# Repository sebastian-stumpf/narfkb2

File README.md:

# narfkb2

More pictures in the `pictures` directory.

## Attention

I'm a hobbyist/amateur at best. So there may be things that aren't optimized. That being said I've had the files
in the `gerbers/` directory manufactured at JLC with 1.6mm size and they work just fine with my fork of the qmk repository
directory. So if you decide to use this, then please be advised that I'm not providing any sort of liability and you should
exercise some caution.

## BOM

| Quantity  | Item                               | Comment                  |
| --------- | ---------------------------------- | ------------------------ |
| 2         | Waveshare RP2040-Zero              |                          |
| 2         | IC-Sockets for MCU                 | Optional but recommended |
| 2         | TRRS Sockets                       |                          |
| 50        | 1N4148 SOD123 diodes               |                          |
| 42        | MX Hotswap Sockets                 |                          |
| 2         | EC11 Encoders                      |                          |
| 6         | Omrom 6mm Tact switches            | B3F-1002                 |
| 42        | MX Switches + Keycaps              |                          |
| 12        | M2 Screws, Nuts, Bolts and Spacers |                          |

## Firmware

See [my fork](https://github.com/sebastian-stumpf/qmk_firmware/tree/sepp/keyboards/narfkb2) of the qmk repository. Nothing special here.
You can just copy the code over to your own repository.

## Feedback

I'm always happy to hear your opinions about this and if you decide to build this board then please do send me a picture of it.

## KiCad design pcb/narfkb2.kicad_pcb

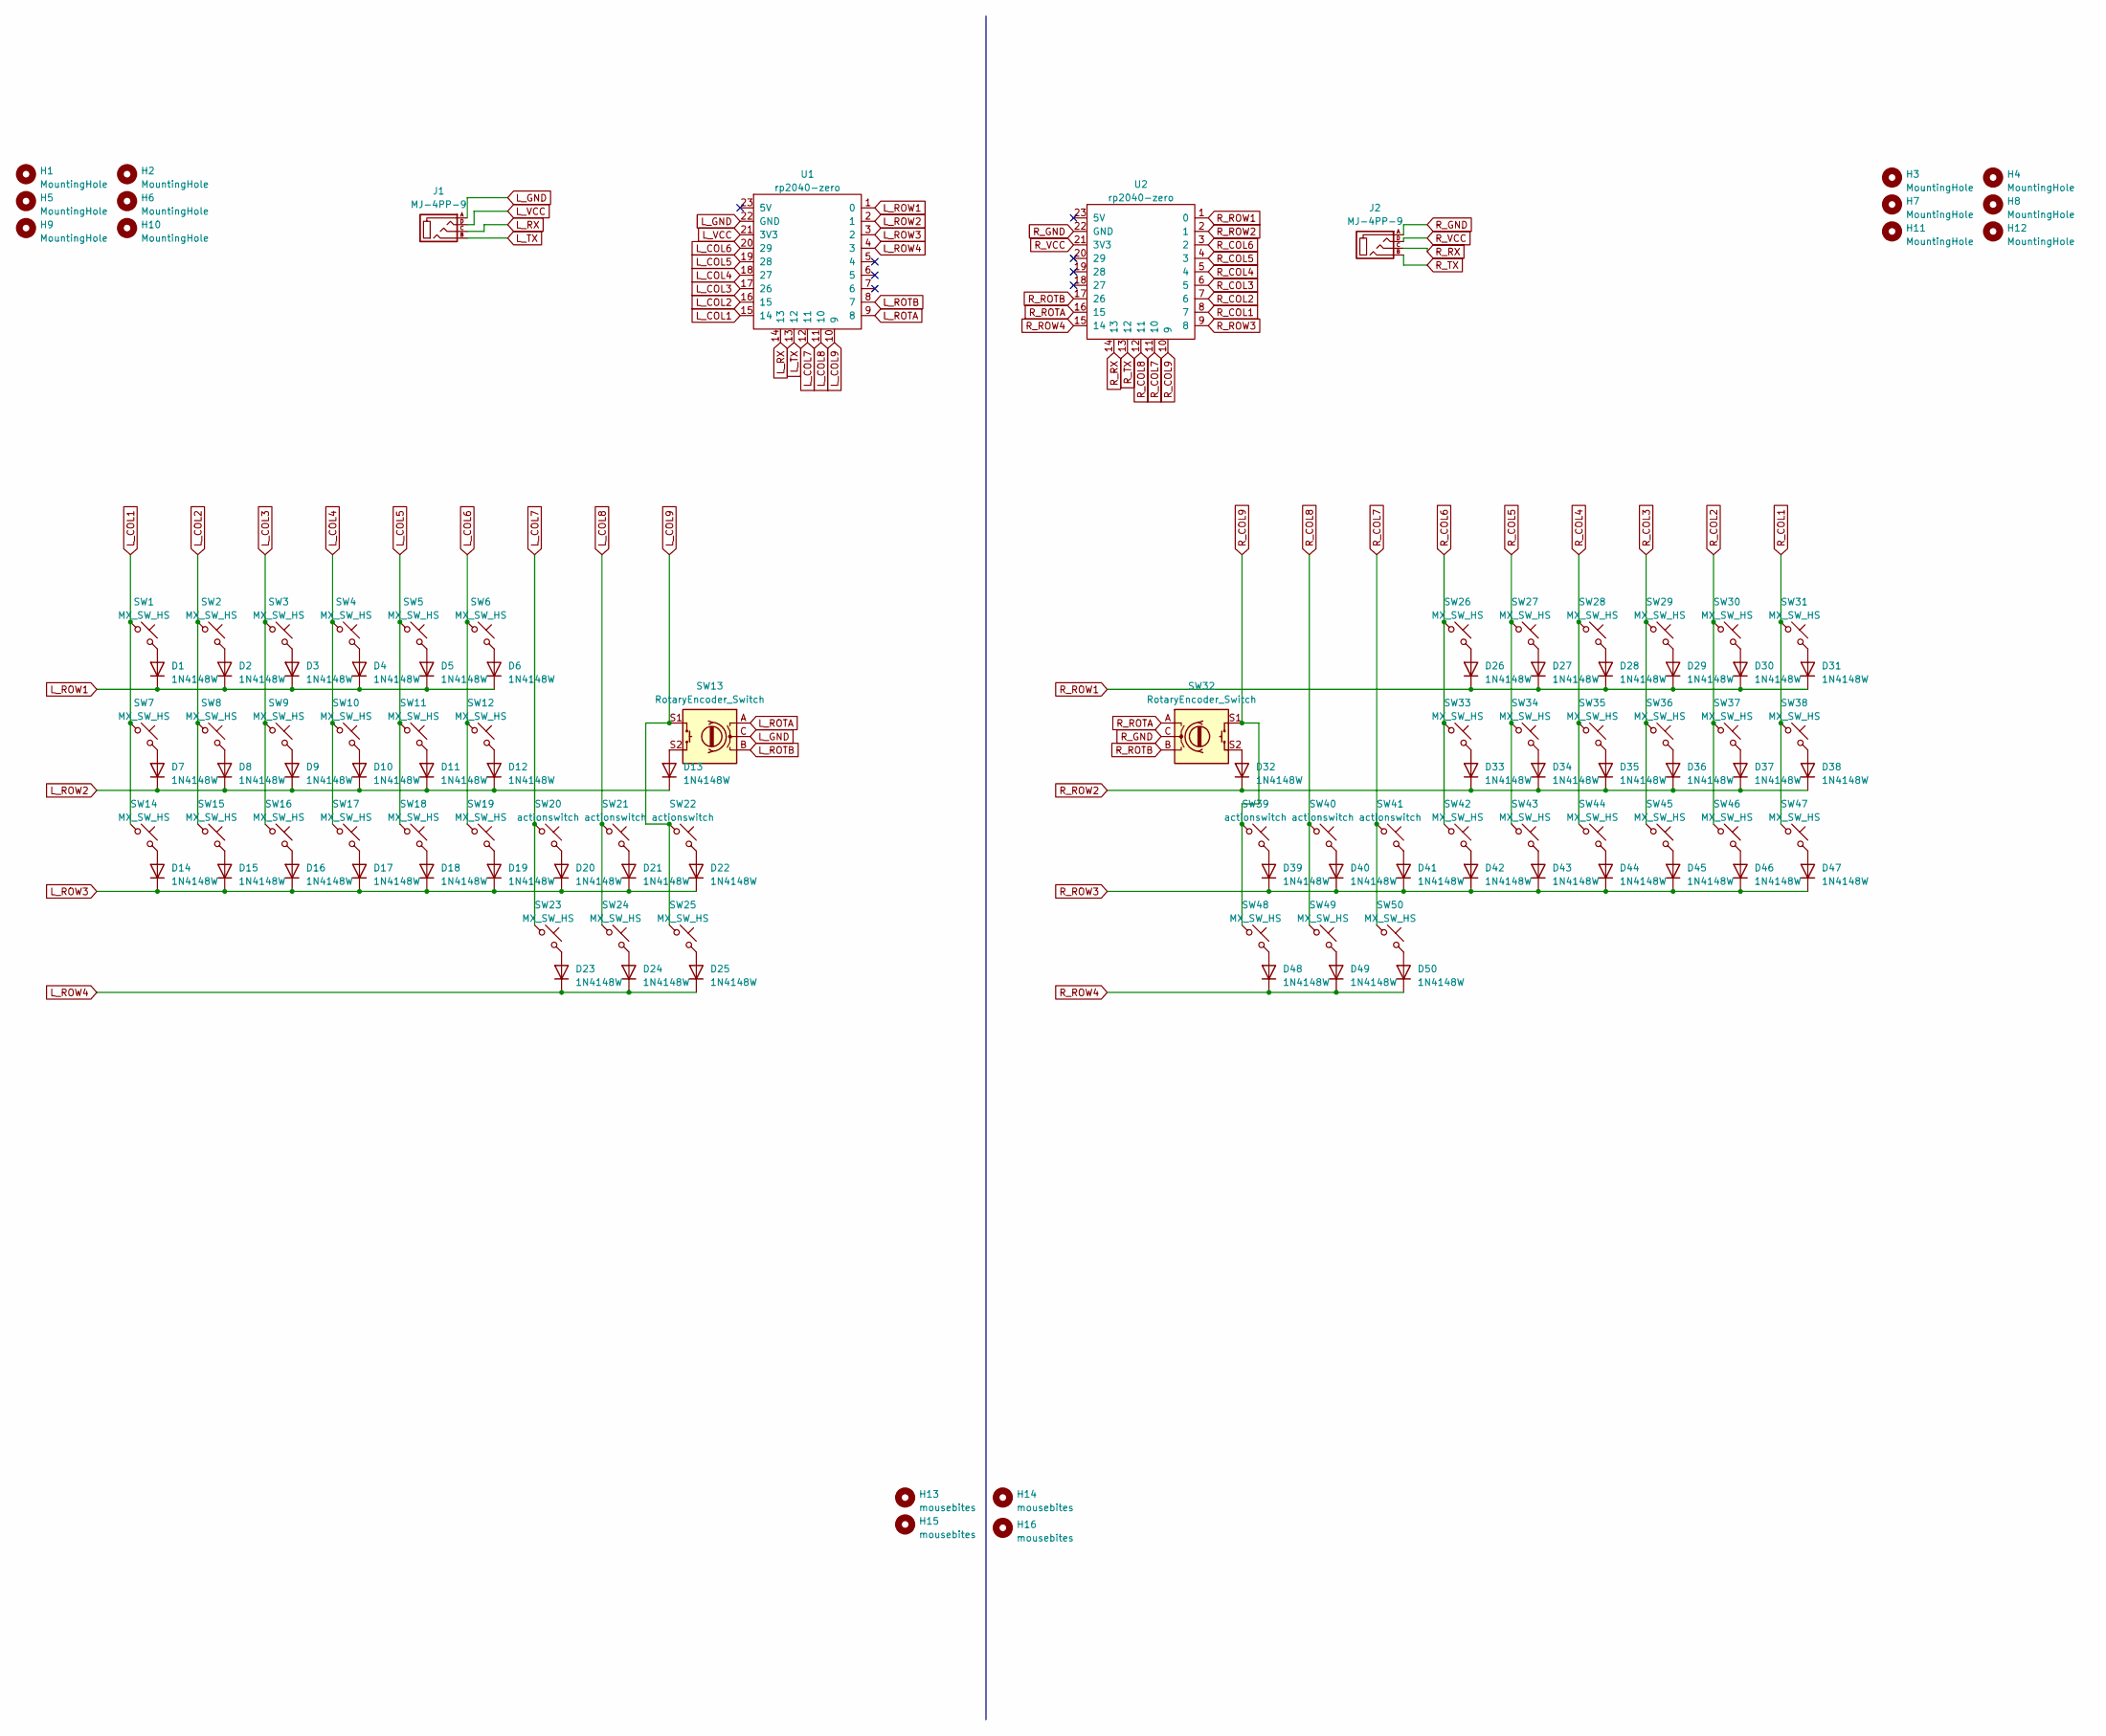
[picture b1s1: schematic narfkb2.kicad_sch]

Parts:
D1, D2, D3, D4, D5, D6, D7, D8, D9, D10, D11, D12, D13, D14, D15, D16, D17, D18, D19, D20, D21, D22, D23, D24, D25, D26, D27, D28, D29, D30, D31, D32, D33, D34, D35, D36, D37, D38, D39, D40, D41, D42, D43, D44, D45, D46, D47, D48, D49, D50: 1N4148W; D_SOD-123
H1, H2, H3, H4, H5, H6, H7, H8, H9, H10, H11, H12: MountingHole; MountingHole_2.2mm_M2_DIN965
H13, H14, H15, H16: mousebites; breakaway-mousebites
J1, J2: MJ-4PP-9
SW1, SW2, SW3, SW4, SW5, SW6, SW7, SW8, SW9, SW10, SW11, SW12, SW14, SW15, SW16, SW17, SW18, SW19, SW23, SW24, SW25, SW26, SW27, SW28, SW29, SW30, SW31, SW33, SW34, SW35, SW36, SW37, SW38, SW42, SW43, SW44, SW45, SW46, SW47, SW48, SW49, SW50: MX_SW_HS; SW_MX_HS_1u
SW13, SW32: RotaryEncoder_Switch; RotaryEncoder_EC11
SW20, SW21, SW22, SW39, SW40, SW41: actionswitch
U1, U2: rp2040-zero; rp2040-zero-tht

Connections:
L_COL1: SW1.1, SW7.1, SW14.1, U1.15 (14)
L_COL2: SW2.1, SW8.1, SW15.1, U1.16 (15)
L_COL3: SW3.1, SW9.1, SW16.1, U1.17 (26)
L_COL4: SW4.1, SW10.1, SW17.1, U1.18 (27)
L_COL5: SW5.1, SW11.1, SW18.1, U1.19 (28)
L_COL6: SW6.1, SW12.1, SW19.1, U1.20 (29)
L_COL7: SW20.1, SW23.1, U1.12 (11)
L_COL8: SW21.1, SW24.1, U1.11 (10)
L_COL9: SW13.S1, SW22.1, SW25.1, U1.10 (9)
L_GND: J1.A, SW13.C, U1.22 (GND)
L_ROTA: SW13.A, U1.9 (8)
L_ROTB: SW13.B, U1.8 (7)
L_ROW1: D1.1 (K), D2.1 (K), D3.1 (K), D4.1 (K), D5.1 (K), D6.1 (K), U1.1 (0)
L_ROW2: D7.1 (K), D8.1 (K), D9.1 (K), D10.1 (K), D11.1 (K), D12.1 (K), D13.1 (K), U1.2 (1)
L_ROW3: D14.1 (K), D15.1 (K), D16.1 (K), D17.1 (K), D18.1 (K), D19.1 (K), D20.1 (K), D21.1 (K), D22.1 (K), U1.3 (2)
L_ROW4: D23.1 (K), D24.1 (K), D25.1 (K), U1.4 (3)
L_RX: J1.C, U1.14 (13)
L_TX: J1.B, U1.13 (12)
L_VCC: J1.D, U1.21 (3V3)
unnamed: D1.2 (A), SW1.2
unnamed: D2.2 (A), SW2.2
unnamed: D3.2 (A), SW3.2
unnamed: D4.2 (A), SW4.2
unnamed: D5.2 (A), SW5.2
unnamed: D6.2 (A), SW6.2
unnamed: D7.2 (A), SW7.2
unnamed: D8.2 (A), SW8.2
unnamed: D9.2 (A), SW9.2
unnamed: D10.2 (A), SW10.2
unnamed: D11.2 (A), SW11.2
unnamed: D12.2 (A), SW12.2
unnamed: D13.2 (A), SW13.S2
unnamed: D14.2 (A), SW14.2
unnamed: D15.2 (A), SW15.2
unnamed: D16.2 (A), SW16.2
unnamed: D17.2 (A), SW17.2
unnamed: D18.2 (A), SW18.2
unnamed: D19.2 (A), SW19.2
unnamed: D20.2 (A), SW20.2
unnamed: D21.2 (A), SW21.2
unnamed: D22.2 (A), SW22.2
unnamed: D23.2 (A), SW23.2
unnamed: D24.2 (A), SW24.2
unnamed: D25.2 (A), SW25.2
unnamed: D26.2 (A), SW26.2
unnamed: D27.2 (A), SW27.2
unnamed: D28.2 (A), SW28.2
unnamed: D29.2 (A), SW29.2
unnamed: D30.2 (A), SW30.2
unnamed: D31.2 (A), SW31.2
unnamed: D32.2 (A), SW32.S2
unnamed: D33.2 (A), SW33.2
unnamed: D34.2 (A), SW34.2
unnamed: D35.2 (A), SW35.2
unnamed: D36.2 (A), SW36.2
unnamed: D37.2 (A), SW37.2
unnamed: D38.2 (A), SW38.2
unnamed: D39.2 (A), SW39.2
unnamed: D40.2 (A), SW40.2
unnamed: D41.2 (A), SW41.2
unnamed: D42.2 (A), SW42.2
unnamed: D43.2 (A), SW43.2
unnamed: D44.2 (A), SW44.2
unnamed: D45.2 (A), SW45.2
unnamed: D46.2 (A), SW46.2
unnamed: D47.2 (A), SW47.2
unnamed: D48.2 (A), SW48.2
unnamed: D49.2 (A), SW49.2
unnamed: D50.2 (A), SW50.2
R_COL1: SW31.1, SW38.1, SW47.1, U2.8 (7)
R_COL2: SW30.1, SW37.1, SW46.1, U2.7 (6)
R_COL3: SW29.1, SW36.1, SW45.1, U2.6 (5)
R_COL4: SW28.1, SW35.1, SW44.1, U2.5 (4)
R_COL5: SW27.1, SW34.1, SW43.1, U2.4 (3)
R_COL6: SW26.1, SW33.1, SW42.1, U2.3 (2)
R_COL7: SW41.1, SW50.1, U2.11 (10)
R_COL8: SW40.1, SW49.1, U2.12 (11)
R_COL9: SW32.S1, SW39.1, SW48.1, U2.10 (9)
R_GND: J2.A, SW32.C, U2.22 (GND)
R_ROTA: SW32.A, U2.16 (15)
R_ROTB: SW32.B, U2.17 (26)
R_ROW1: D26.1 (K), D27.1 (K), D28.1 (K), D29.1 (K), D30.1 (K), D31.1 (K), U2.1 (0)
R_ROW2: D32.1 (K), D33.1 (K), D34.1 (K), D35.1 (K), D36.1 (K), D37.1 (K), D38.1 (K), U2.2 (1)
R_ROW3: D39.1 (K), D40.1 (K), D41.1 (K), D42.1 (K), D43.1 (K), D44.1 (K), D45.1 (K), D46.1 (K), D47.1 (K), U2.9 (8)
R_ROW4: D48.1 (K), D49.1 (K), D50.1 (K), U2.15 (14)
R_RX: J2.C, U2.14 (13)
R_TX: J2.B, U2.13 (12)
R_VCC: J2.D, U2.21 (3V3)

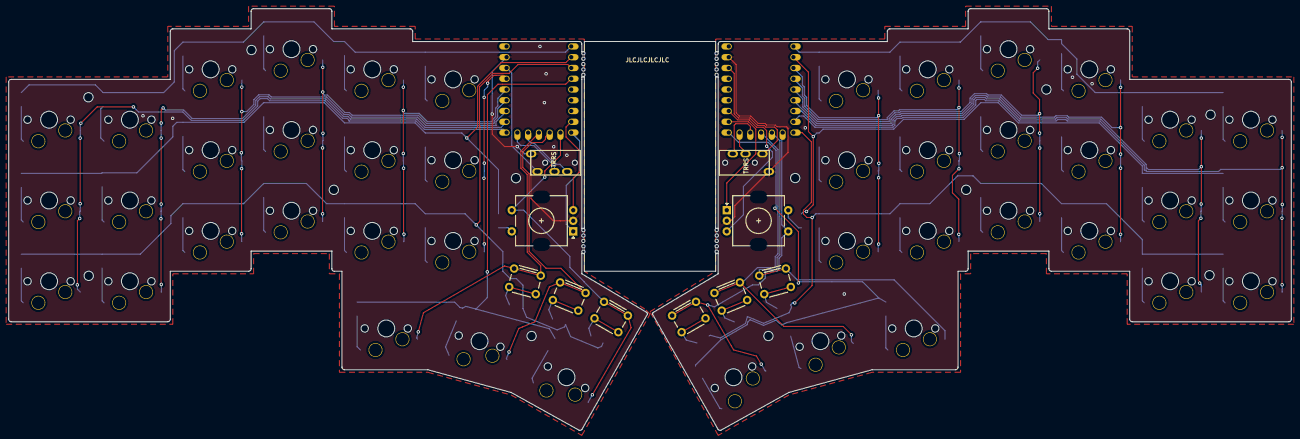
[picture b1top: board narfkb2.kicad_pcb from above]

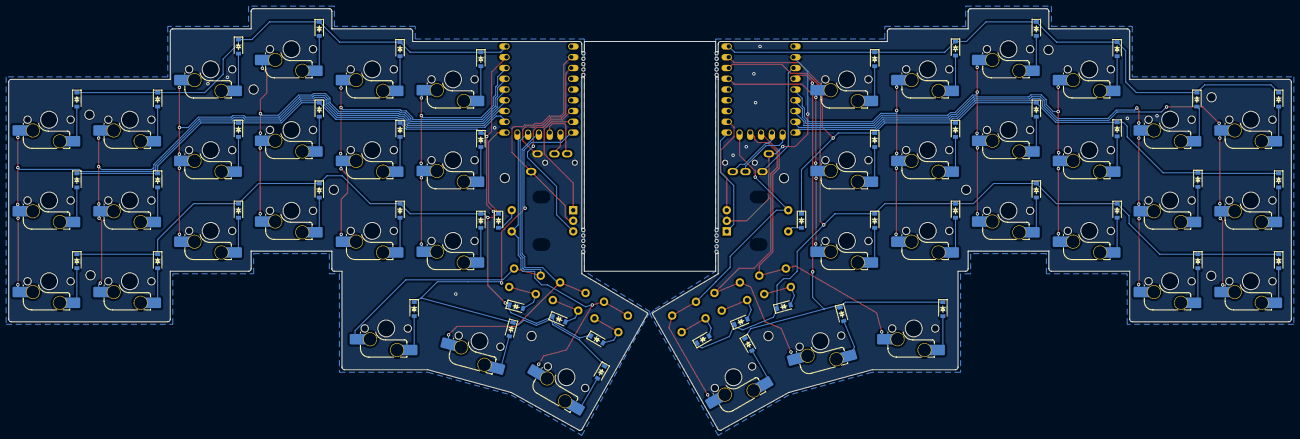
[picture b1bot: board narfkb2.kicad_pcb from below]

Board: 2 copper layers, 302.4 x 99.4 mm, 120 parts (50 on the bottom side), 88 nets.

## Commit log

2023-05-11 Create LICENSE
